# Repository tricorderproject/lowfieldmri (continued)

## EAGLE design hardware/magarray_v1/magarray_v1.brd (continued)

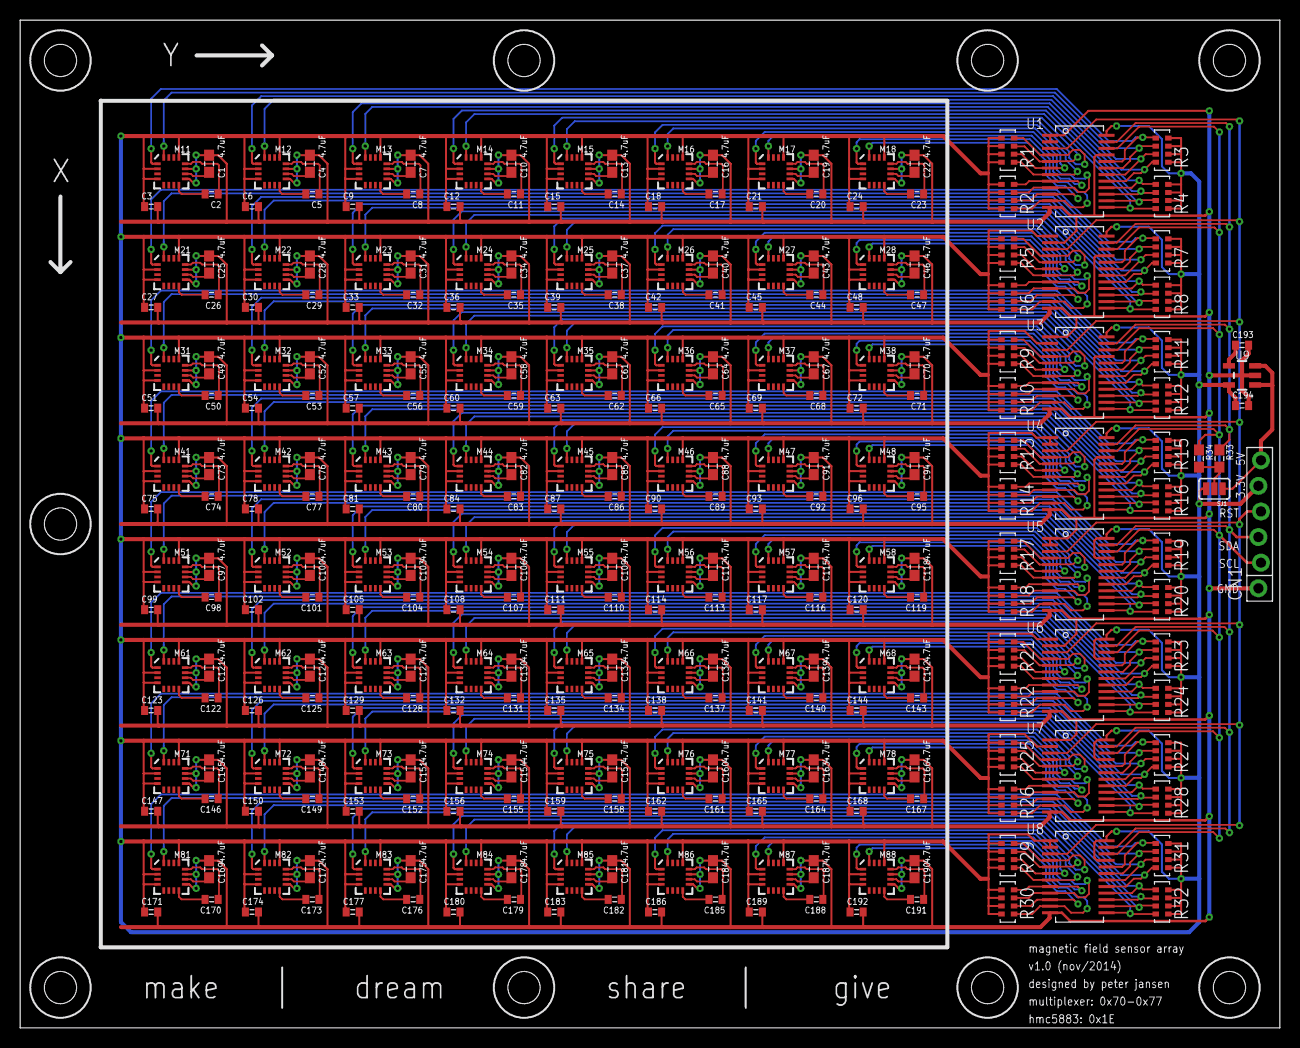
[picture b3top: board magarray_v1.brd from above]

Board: 2 copper layers, 125.0 x 100.0 mm, 303 parts (0 on the bottom side), 328 nets.

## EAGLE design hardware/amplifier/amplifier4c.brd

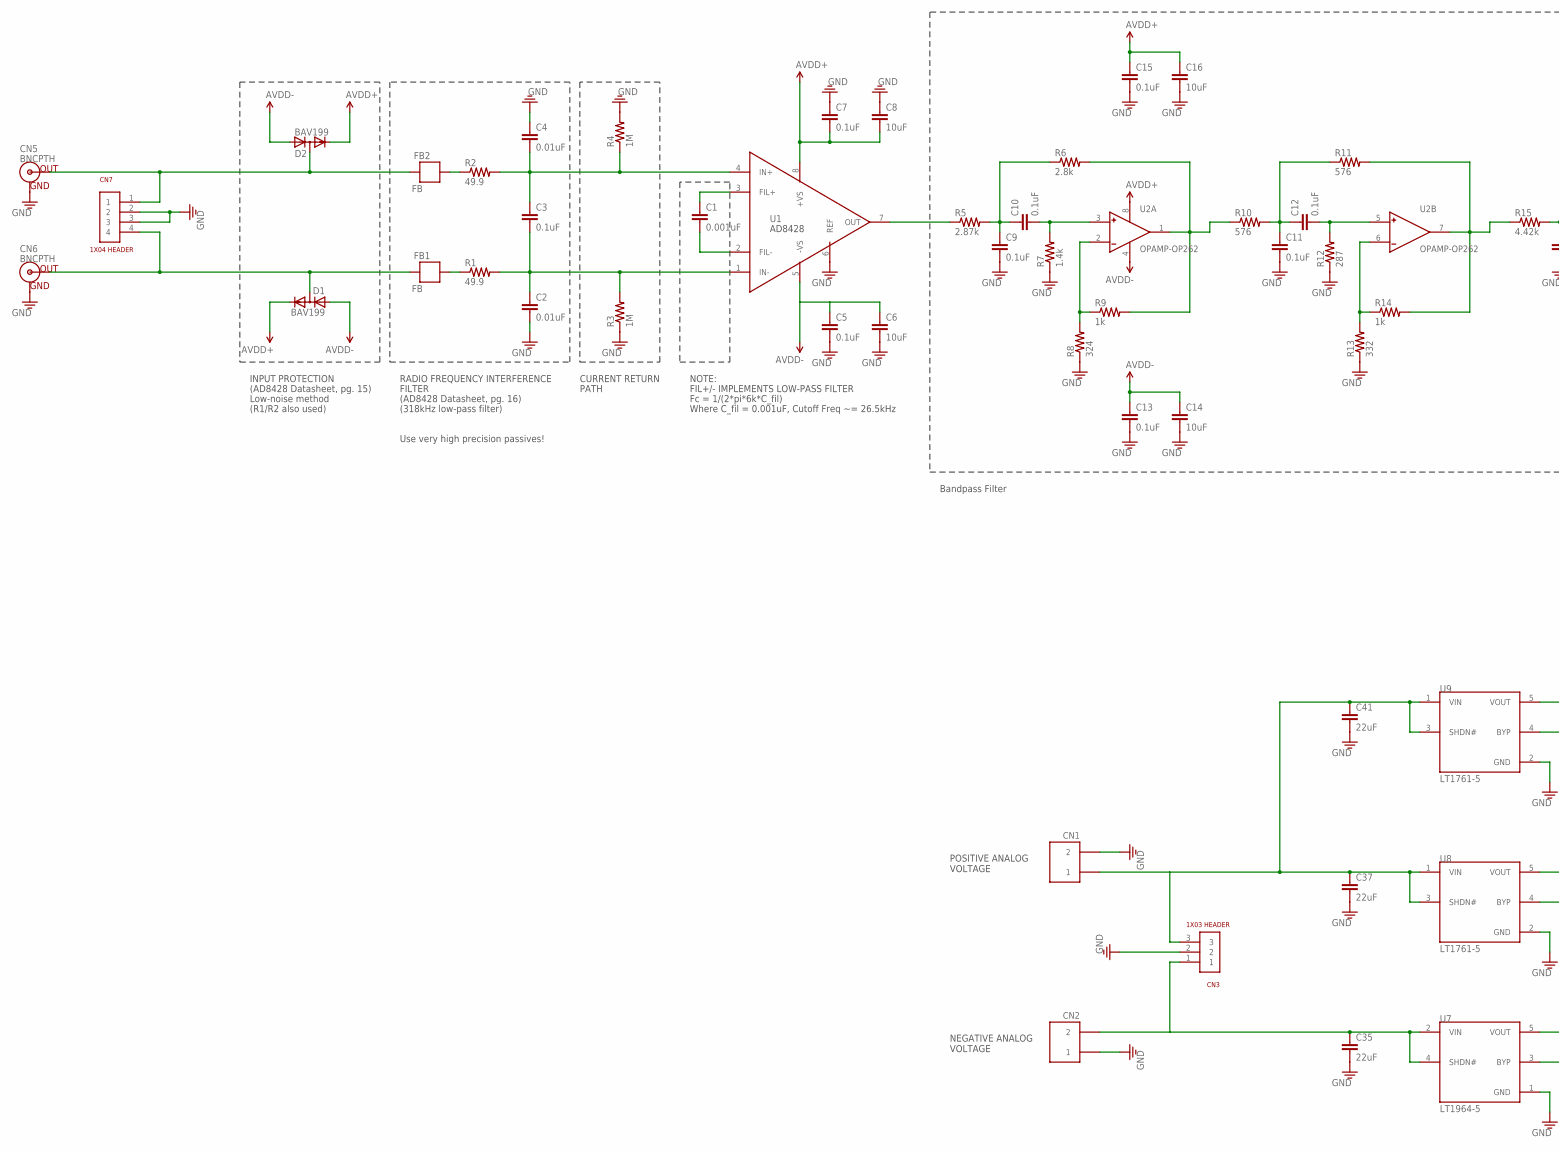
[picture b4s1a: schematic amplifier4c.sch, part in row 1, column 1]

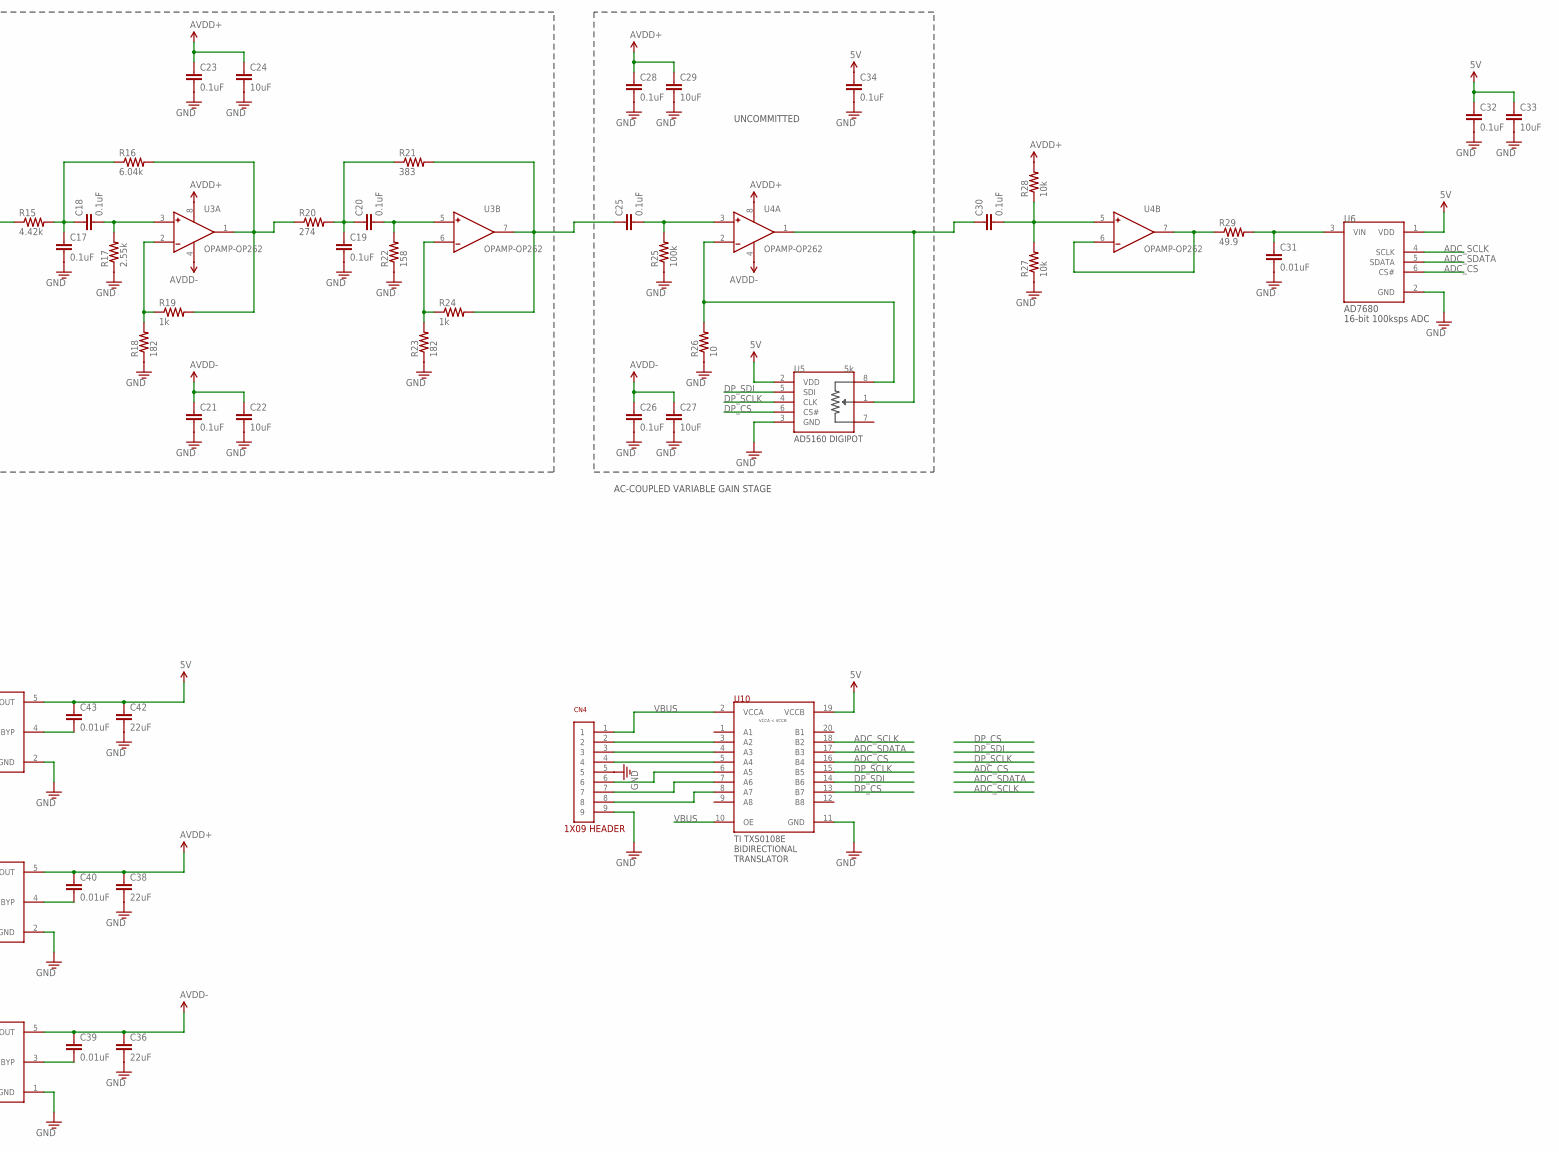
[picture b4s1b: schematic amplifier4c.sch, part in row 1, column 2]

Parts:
C1: 0.001uF; 0603
C2, C4, C31, C39, C40, C43: 0.01uF; 0603
C3, C5, C7, C9, C10, C11, C12, C13, C15, C17, C18, C19, C20, C21, C23, C25, C26, C28, C30, C32, C34: 0.1uF; 0603
C6, C8, C14, C16, C22, C24, C27, C29, C33: 10uF; 0805
C35, C36, C37, C38, C41, C42: 22uF; 1206
CN1, CN2: SCREWTERMINAL-2PIN
CN3: 1X03
CN4: 1X09
CN5, CN6: BNCPTH; BNC
CN7: 1X04
D1, D2: BAV199; SOT23
FB1, FB2: FB; 0603
R1, R2, R29: 49.9; 0603
R3, R4: 1M; 0603
R5: 2.87k; 0603
R6: 2.8k; 0603
R7: 1.4k; 0603
R8: 324; 0603
R9, R14, R19, R24: 1k; 0603
R10, R11: 576; 0603
R12: 287; 0603
R13: 332; 0603
R15: 4.42k; 0603
R16: 6.04k; 0603
R17: 2.55k; 0603
R18, R23: 182; 0603
R20: 274; 0603
R21: 383; 0603
R22: 158; 0603
R25: 100k; 0603
R26: 10; 0603
R27, R28: 10k; 0603
U1: OPAMP-AD8428; SOIC-8
U2, U3, U4: OPAMP-OP262; SOIC-8
U5: 5k; SOT-23-8
U6: ADC-AD7680; SOT-23-6L
U7: LT1964-5; SOT-23-5L
U8, U9: LT1761-5; SOT-23-5L
U10: TRANSLATOR-TXS0108E; TSSOP-20

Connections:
5V: C32.1, C33.1, C34.1, C42.1, C43.1, U5.2 (VDD), U6.1 (VDD), U9.5 (VOUT), U10.19 (VCCB)
ADC_CS: U6.6 (CS#), U10.16 (B4)
ADC_SCLK: U6.4 (SCLK), U10.18 (B2)
ADC_SDATA: U6.5 (SDATA), U10.17 (B3)
AVDD+: C7.2, C8.2, C15.1, C16.1, C23.1, C24.1, C28.1, C29.1, C38.1, C40.1, D1.2 (C), D2.2 (C), R28.2, U1.8 (+VS), U2.8 (V+), U3.8 (V+), U4.8 (V+), U8.5 (VOUT)
AVDD-: C5.1, C6.1, C13.1, C14.1, C21.1, C22.1, C26.1, C27.1, C36.1, C39.1, D1.1 (A), D2.1 (A), U1.5 (-VS), U2.4 (V-), U3.4 (V-), U4.4 (V-), U7.5 (VOUT)
DP_CS: U5.6 (CS#), U10.13 (B7)
DP_SCLK: U5.4 (CLK), U10.15 (B5)
DP_SDI: U5.5 (SDI), U10.14 (B6)
GND: C2.2, C4.1, C5.2, C6.2, C7.1, C8.1, C9.2, C11.2, C13.2, C14.2, C15.2, C16.2, C17.2, C19.2, C21.2, C22.2, C23.2, C24.2, C26.2, C27.2, C28.2, C29.2, C31.2, C32.2, C33.2, C34.2, C35.2, C36.2, C37.2, C38.2, C41.2, C42.2, CN1.2, CN2.1, CN3.2, CN4.5, CN4.9, CN5.GND, CN6.GND, CN7.2, CN7.3, R3.1, R4.2, R7.1, R8.1, R12.1, R13.1, R17.1, R18.1, R22.1, R23.1, R25.1, R26.1, R27.1, U1.6 (REF), U5.3 (GND), U6.2 (GND), U7.1 (GND), U8.2 (GND), U9.2 (GND), U10.11 (GND)
unnamed: C1.1, U1.3 (FIL+)
unnamed: C1.2, U1.2 (FIL-)
unnamed: C3.1, C4.2, R2.2, R4.1, U1.4 (IN+)
unnamed: C2.1, C3.2, R1.2, R3.2, U1.1 (IN-)
unnamed: C9.1, C10.1, R5.2, R6.1
unnamed: FB1.1, R1.1
unnamed: FB2.1, R2.1
unnamed: CN6.S (OUT), CN7.4, D1.3 (AC), FB1.2
unnamed: CN5.S (OUT), CN7.1, D2.3 (AC), FB2.2
unnamed: C10.2, R7.2, U2.3 (+)
unnamed: R8.2, R9.1, U2.2 (-)
unnamed: R5.1, U1.7 (OUT)
unnamed: R6.2, R9.2, R10.1, U2.1 (OUT)
unnamed: C25.2, R25.2, U4.3 (+)
unnamed: C11.1, C12.1, R10.2, R11.1
unnamed: C12.2, R12.2, U2.5 (+)
unnamed: R13.2, R14.1, U2.6 (-)
unnamed: R11.2, R14.2, R15.1, U2.7 (OUT)
unnamed: C17.1, C18.1, R15.2, R16.1
unnamed: C18.2, R17.2, U3.3 (+)
unnamed: R18.2, R19.1, U3.2 (-)
unnamed: R16.2, R19.2, R20.1, U3.1 (OUT)
unnamed: C19.1, C20.1, R20.2, R21.1
unnamed: C20.2, R22.2, U3.5 (+)
unnamed: R23.2, R24.1, U3.6 (-)
unnamed: C25.1, R21.2, R24.2, U3.7 (OUT)
unnamed: R26.2, U4.2 (-), U5.8 (A)
unnamed: C30.1, U4.1 (OUT), U5.1 (W)
unnamed: C31.1, R29.2, U6.3 (VIN)
unnamed: C30.2, R27.2, R28.1, U4.5 (+)
unnamed: R29.1, U4.6 (-), U4.7 (OUT)
unnamed: CN4.2, U10.3 (A2)
unnamed: CN4.3, U10.4 (A3)
unnamed: CN4.4, U10.5 (A4)
unnamed: CN4.6, U10.6 (A5)
unnamed: CN4.7, U10.7 (A6)
unnamed: CN4.8, U10.8 (A7)
unnamed: C40.2, U8.4 (BYP)
unnamed: C43.2, U9.4 (BYP)
unnamed: C39.2, U7.3 (BYP)
VBUS: CN4.1, U10.2 (VCCA), U10.10 (OE)
VIN+: C37.1, C41.1, CN1.1, CN3.3, U8.1 (VIN), U8.3 (SHDN#), U9.1 (VIN), U9.3 (SHDN#)
VIN-: C35.1, CN2.2, CN3.1, U7.2 (VIN), U7.4 (SHDN#)

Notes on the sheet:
FIL+/- IMPLEMENTS LOW-PASS FILTER
Fc = 1/(2*pi*6k*C_fil)
Where C_fil = 0.001uF, Cutoff Freq ~= 26.5kHz
NOTE:
INPUT PROTECTION
(AD8428 Datasheet, pg. 15)
Low-noise method
CURRENT RETURN
PATH
RADIO FREQUENCY INTERFERENCE
FILTER
(R1/R2 also used)
(318kHz low-pass filter)
(AD8428 Datasheet, pg. 16)
Use very high precision passives!
Bandpass Filter
UNCOMMITTED
AC-COUPLED VARIABLE GAIN STAGE
POSITIVE ANALOG VOLTAGE
NEGATIVE ANALOG VOLTAGE

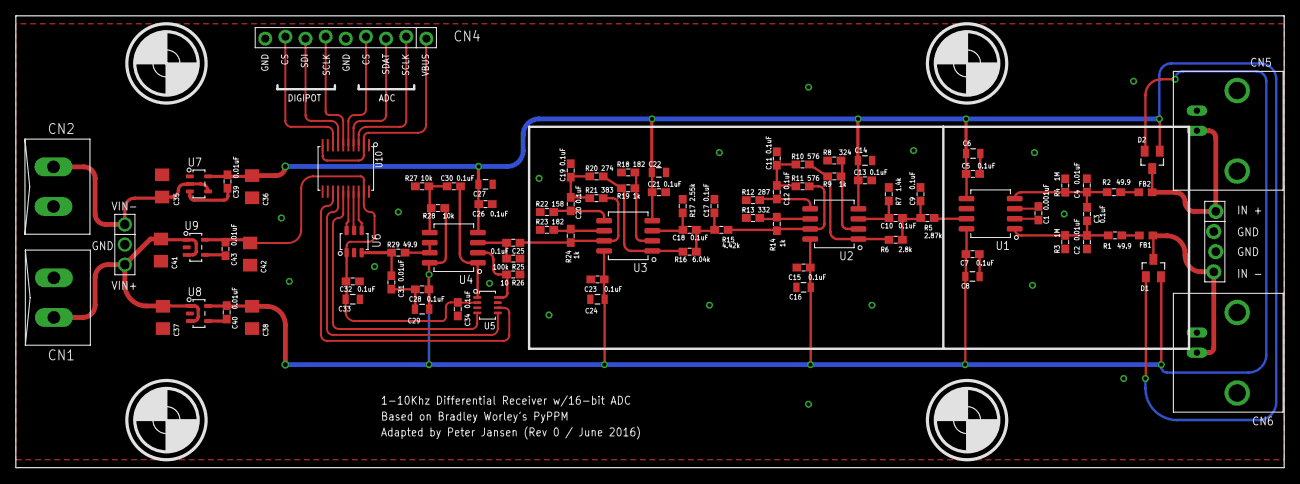
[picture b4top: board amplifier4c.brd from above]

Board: 2 copper layers, 160.0 x 57.0 mm, 93 parts (0 on the bottom side), 53 nets.

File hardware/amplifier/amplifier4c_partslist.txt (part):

Partlist

Exported from amplifier4c.sch at 12/06/2016 5:14:38 PM

EAGLE Version 6.5.0 Copyright (c) 1988-2013 CadSoft

Assembly variant: 

Part     Value               Device              Package            Library             Sheet

C1       0.001uF             CAP0603             0603               lowfieldmri         1
C2       0.01uF              CAP0603             0603               lowfieldmri         1
C3       0.1uF               CAP0603             0603               lowfieldmri         1
C4       0.01uF              CAP0603             0603               lowfieldmri         1
C5       0.1uF               CAP0603             0603               lowfieldmri         1
C6       10uF                CAP0805             0805               lowfieldmri         1
C7       0.1uF               CAP0603             0603               lowfieldmri         1
C8       10uF                CAP0805             0805               lowfieldmri         1
C9       0.1uF               CAP0603             0603               lowfieldmri         1
C10      0.1uF               CAP0603             0603               lowfieldmri         1
C11      0.1uF               CAP0603             0603               lowfieldmri         1
C12      0.1uF               CAP0603             0603               lowfieldmri         1
C13      0.1uF               CAP0603             0603               lowfieldmri         1
C14      10uF                CAP0805             0805               lowfieldmri         1
C15      0.1uF               CAP0603             0603               lowfieldmri         1
C16      10uF                CAP0805             0805               lowfieldmri         1
C17      0.1uF               CAP0603             0603               lowfieldmri         1
C18      0.1uF               CAP0603             0603               lowfieldmri         1
C19      0.1uF               CAP0603             0603               lowfieldmri         1
C20      0.1uF               CAP0603             0603               lowfieldmri         1
C21      0.1uF               CAP0603             0603               lowfieldmri         1
C22      10uF                CAP0805             0805               lowfieldmri         1
C23      0.1uF               CAP0603             0603               lowfieldmri         1
C24      10uF                CAP0805             0805               lowfieldmri         1
C25      0.1uF               CAP0603             0603               lowfieldmri         1
C26      0.1uF               CAP0603             0603               lowfieldmri         1
C27      10uF                CAP0805             0805               lowfieldmri         1
C28      0.1uF               CAP0603             0603               lowfieldmri         1
C29      10uF                CAP0805             0805               lowfieldmri         1
C30      0.1uF               CAP0603             0603               lowfieldmri         1
C31      0.01uF              CAP0603             0603               lowfieldmri         1
C32      0.1uF               CAP0603             0603               lowfieldmri         1
C33      10uF                CAP0805             0805               lowfieldmri         1
C34      0.1uF               CAP0603             0603               lowfieldmri         1
C35      22uF                CAP1206             1206               SparkFun-Capacitors 1
C36      22uF                CAP1206             1206               SparkFun-Capacitors 1
C37      22uF                CAP1206             1206               SparkFun-Capacitors 1
C38      22uF                CAP1206             1206               SparkFun-Capacitors 1
C39      0.01uF              CAP0603             0603               lowfieldmri         1
C40      0.01uF              CAP0603             0603               lowfieldmri         1
C41      22uF                CAP1206             1206               SparkFun-Capacitors 1
C42      22uF                CAP1206             1206               SparkFun-Capacitors 1
C43      0.01uF              CAP0603             0603               lowfieldmri         1
CN1      SCREWTERMINAL-2PIN  SCREWTERMINAL-2PIN  SCREWTERMINAL-2PIN openct              1
CN2      SCREWTERMINAL-2PIN  SCREWTERMINAL-2PIN  SCREWTERMINAL-2PIN openct              1
CN3      1X03                1X03                1X03               openct              1
CN4      1X09                1X09                1X09               lowfieldmri         1
CN5      BNCPTH              BNCPTH              BNC                SparkFun-Connectors 1
CN6      BNCPTH              BNCPTH              BNC                SparkFun-Connectors 1
CN7      1X04                1X04                1X04               lowfieldmri         1
D1       BAV199              BAV199              SOT23              diode               1
D2       BAV199              BAV199              SOT23              diode               1
FB1      FB                  FB                  0603               SparkFun-Passives   1
FB2      FB                  FB                  0603               SparkFun-Passives   1
R1       49.9                RESISTOR0603        0603               lowfieldmri         1
R2       49.9                RESISTOR0603        0603               lowfieldmri         1
R3       1M                  RESISTOR0603        0603               lowfieldmri         1
R4       1M                  RESISTOR0603        0603               lowfieldmri         1
R5       2.87k               RESISTOR0603        0603               lowfieldmri         1
R6       2.8k                RESISTOR0603        0603               lowfieldmri         1
R7       1.4k                RESISTOR0603        0603               lowfieldmri         1
R8       324                 RESISTOR0603        0603               lowfieldmri         1
R9       1k                  RESISTOR0603        0603               lowfieldmri         1
R10      576                 RESISTOR0603        0603               lowfieldmri         1
R11      576                 RESISTOR0603        0603               lowfieldmri         1
R12      287                 RESISTOR0603        0603               lowfieldmri         1
R13      332                 RESISTOR0603        0603               lowfieldmri         1
R14      1k                  RESISTOR0603        0603               lowfieldmri         1
R15      4.42k               RESISTOR0603        0603               lowfieldmri         1
R16      6.04k               RESISTOR0603        0603               lowfieldmri         1
R17      2.55k               RESISTOR0603        0603               lowfieldmri         1
R18      182                 RESISTOR0603        0603               lowfieldmri         1
R19      1k                  RESISTOR0603        0603               lowfieldmri         1
R20      274                 RESISTOR0603        0603               lowfieldmri         1
R21      383                 RESISTOR0603        0603               lowfieldmri         1
R22      158                 RESISTOR0603        0603               lowfieldmri         1
R23      182                 RESISTOR0603        0603               lowfieldmri         1
R24      1k                  RESISTOR0603        0603               lowfieldmri         1
R25      100k                RESISTOR0603        0603               lowfieldmri         1
R26      10                  RESISTOR0603        0603               lowfieldmri         1
R27      10k                 RESISTOR0603        0603               lowfieldmri         1
R28      10k                 RESISTOR0603        0603               lowfieldmri         1
R29      49.9                RESISTOR0603        0603               lowfieldmri         1
U1       OPAMP-AD8428        OPAMP-AD8428        SOIC-8             lowfieldmri         1
U2       OPAMP-OP262         OPAMP-OP262         SOIC-8             lowfieldmri         1
U3       OPAMP-OP262         OPAMP-OP262         SOIC-8             lowfieldmri         1
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
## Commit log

2016-06-13 added initial readme
2016-06-22 Added PDF of schematic
2016-06-23 Added HMC5883L magnetometer array board, version 1, from first iteration of the project
2016-06-23 Added version 1 of the simulator, from the first iteration of the project
2016-07-11 Added MLX90393 magnetometer breakout board schematics/board artwork
2021-12-01 added teensy test code for radio
2021-12-01 small additions
2021-12-01 added simple matplotlib plot to radio data coming in
2021-12-02 Added working Teensy code, verified with logic analyzer (including fixing digipot bug)
2022-03-19 minor changes
